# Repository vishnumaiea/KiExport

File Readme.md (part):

# KiExport

[**KiExport**](https://github.com/vishnumaiea/KiExport) is a Python application for automating the manufacturing files generation process from KiCad PCB design projects. This is a CLI (Command Line Interface) utility. Commands and arguments can be passed to the script while running, or from a JSON configuration file named `kiexport.json`. You should be familiar working with CLI tools and how to execute commands from a terminal.

KiExport generates the manufacturing files based on the options available in the `kiexport.json` file, and saves them in an organized way. It renames the files, folders and create ZIP archive files with proper names and date stamps so that you can send them to a manufacturer or client easily. Since the `kiexport.json` configuration file can be edited for any project, you only have to create the file once. You can also create multiple configuration files according to different manufacturing requirements.

The [**Mitayi Pico RP2040**](https://github.com/CIRCUITSTATE/Mitayi-Pico-RP2040) project is added as a sample project to test the script. If you are on Windows, you can run the `EXPORT-ALL.bat` batch script, or if you're on MacOS, you can run the `EXPORT-ALL.sh` script to automatically generate the manufacturing files.

This tool is not yet tested with Linux.

- **Author:** [Vishnu Mohanan](https://github.com/vishnumaiea)
- **Version:** `0.3.0`
- **Contributors:** Dominic Le Blanc ([@domleblanc94](https://github.com/domleblanc94)), Leor Weinstein

This tool was created with the help of [**ChatGPT**](https://chat.openai.com/chat). Thanks to humanity!

## Table of Contents
- [KiExport](#kiexport)
  - [Table of Contents](#table-of-contents)
  - [Why?](#why)
  - [Why not KiCad Jobsets?](#why-not-kicad-jobsets)
  - [Requirements](#requirements)
  - [Installation](#installation)
    - [Windows](#windows)
    - [MacOS](#macos)
  - [Example](#example)
  - [Usage](#usage)
  - [Commands](#commands)
    - [`version`](#version)
    - [`help`](#help)
    - [`pcb_drc`](#pcb_drc)
    - [`gerbers`](#gerbers)
    - [`drills`](#drills)
    - [`positions`](#positions)
    - [`pcb_pdf`](#pcb_pdf)
    - [`pcb_render`](#pcb_render)
    - [`sch_pdf`](#sch_pdf)
    - [`ddd`](#ddd)
    - [`pcb_svg`](#pcb_svg)
    - [`bom`](#bom)
    - [`run`](#run)
  - [Configuration File](#configuration-file)
  - [Log File](#log-file)
  - [License](#license)
  - [References](#references)

## Why?

- ~~Currently, exporting manufacturing files from KiCad's own UI requires setting so many options correctly and moving through different steps for different types of files.~~
- If you make a mistake in choosing the options correctly, you will end up with a "bad" manufacturing file that will waste your time later.
- ~~KiCad currently has no ability to save the export options as presets and it does not always remember the previously used options.~~
- Existing plugins available for KiCad only work for specific types of files and specific set of manufacturing options.
- The number and types of files generated from a KiCad project can be quite many. Renaming, organizing and archiving the files manually can be a tedious task. For example, we generate Gerbers, PCB PDF, Schematic PDF, STEP, VRML, CSV BoM, HTML BoM, XLS BoM, Position Files, and Preview Images for a typical project. We have to do this every time we make a change to the project to keep consistency across the set of files generated at a time.
- KiCad CLI can do almost all of what the KiCad UI can.
- Instead of typing the arguments manually to a terminal all the time, we can save the options as a JSON file and call the KiCad CLI every time we want to generate the files.

## Why not KiCad Jobsets?

KiCad V9 added support for **Jobsets** which allow you to generate manufacturing files in an automated way. However, the feature is in its early stages and causes freezes and crashes often (at least when I tried it last time). Until the feature matures enough, the development on KiExport will continue.

## Requirements

This software was developed and tested on Windows 11. It should work on other platforms as well, but it is not tested. The following software should be installed in your system to use this tool.

- [Python 3.x](https://www.python.org/downloads/)
- [KiCad 8.x or later](https://www.kicad.org/download/)
- [Git](https://git-scm.com/downloads) (Optional)
- [Interactive HTML BoM Plugin](https://github.com/openscopeproject/InteractiveHtmlBom) (Optional, if you want to generate HTML BoM)
- [VTracer](https://github.com/visioncortex/vtracer) (Optional, if you want to generate SVG renderings)
- Recommended:
  - [VS Code](https://code.visualstudio.com/download)
  - [Windows Terminal](https://github.com/microsoft/terminal/releases) (for Windows only)

## Installation

KiExport relies on the [**KiCad-CLI**](https://docs.kicad.org/10.0/en/cli/cli.html) tool to generate the files and therefore supports all the features of KiCad-CLI. You should have a KiCad version installed in your system to use this tool. You can download and install the latest version of KiCad from [here](https://kicad.org/download/).

### Windows

After installing KiCad, browse to the installation folder and find the `bin` directory where the `kicad-cli.exe` file is located. Add the `bin` folder to your system `PATH`. If you do not know how to add a new path to the system `PATH` variable, check out any tutorials on the internet. If you do not want to add the `kicad-cli` file to the `PATH`, then you can provide the complete path of the **kicad-cli.exe** file in the JSON configuration file using the `kicad_cli_path` parameter. This allows you to have multiple versions of KiCad and use them for different projects.

### MacOS

After installing KiCad, browse to the `Applications` folder and find the `KiCad` application icon. Right click on the icon and click "Show Package Contents" to navigate to the `Contents/MacOS` directory where the `kicad-cli` file is located. Copy the path of the `kicad-cli` file by right clicking on the file and selecting "Copy as Pathname" (for example `/Applications/KiCad/KiCad.app/Contents/MacOS/kicad-cli`) and add it to the JSON configuration file using the `kicad_cli_path` parameter. This allows you to have multiple versions of KiCad and use them for different projects.

You can clone/fork the project to obtain a copy of the repository in your system using the following command. [Git](https://git-scm.com/downloads) should be installed and available on the path.

```bash
git clone https://github.com/vishnumaiea/KiExport.git
```

Additionally, you can download the project as a ZIP file from the main page or the [Releases](/releases) page and extract it in your system. After getting the files, you can add the project folder to the system `PATH` variable. If your system opens Python script files with the Python interpreter by default, you can run any python script directly from the terminal even without using the `.py` extension as shown in the image below.

If it still says "kiexport" is not a valid command, add the `.PY` extension to the `PATHEXT` system environment variable in Windows as shown below.

If you are going to run the app as a Python script, install the dependencies using the following command.

```bash
pip install -r requirements.txt
```

Additionally, the app can tell you which dependencies are missing in most cases, and guide you to install them. If you do not want to run KiEXport as a Python script, or if you do not want to setup Python in your system, then you can use the Windows executable directly. The executable is available in the [`dist`](/dist/) folder. You can add the `dist` folder to your system `PATH` variable to run the app from anywhere in the terminal.

Check if the app is working by checking the version of the tool. Open a terminal and run the following command.

```bash
kiexport -v
```

If you see the version printed, the installation is successful. Otherwise, follow the installation procedure again.

## Example

Following is a tree view of the files generated by KiExport from the **Mitayi-Pico-D1** project. A top level revision folder will be created to store the files for that specific revision. Under that, a date-specific folder will be created to store files generated in a specific day. Inside that, file-specific folders are created to store the different types of files. ZIP archives are created for some type of files that are usually sent as a set of files to the manufacturer, for example Gerbers.

If you generate the files multiple times a day, older files will be overwritten except for any files with a sequence number at the end of the filename. For example, ZIP files have a sequence number at the end of the filename after the date string. A new file with a new sequence number will be created when multiple files are generated.

```
\---R0.6
    \---2024-10-26
        +---3D
        |       Mitayi-Pico-RP2040-R0.6-STEP-26102024-1.step
        |       Mitayi-Pico-RP2040-R0.6-VRML-26102024-1.wrl
        |       Mitayi-Pico-RP2040-R0.6-3DPDF-26102024-1.pdf
        |
        +---Position
        |       Mitayi-Pico-RP2040-R0.6-Position-All.csv
        |       Mitayi-Pico-RP2040-R0.6-Position-Back.csv 
        |       Mitayi-Pico-RP2040-R0.6-Position-Front.csv
        |       Mitayi-Pico-RP2040-R0.6-Position-Files-26102024-1.zip
        |
        +---BoM
        |       Mitayi-Pico-RP2040-R0.6-BoM-CSV-26102024-1.csv
        |       Mitayi-Pico-RP2040-R0.6-BoM-XLS-26102024-1.xlsx
        |       Mitayi-Pico-RP2040-R0.6-BoM-HTML-26102024-1.html
        |
        +---Gerber
        |       Mitayi-Pico-RP2040-R0.6-B_Courtyard.gbr
        |       Mitayi-Pico-RP2040-R0.6-B_Cu.gbr
        |       Mitayi-Pico-RP2040-R0.6-B_Fab.gbr
        |       Mitayi-Pico-RP2040-R0.6-B_Mask.gbr
        |       Mitayi-Pico-RP2040-R0.6-B_Paste.gbr
        |       Mitayi-Pico-RP2040-R0.6-B_Silkscreen.gbr
        |       Mitayi-Pico-RP2040-R0.6-Edge_Cuts.gbr
        |       Mitayi-Pico-RP2040-R0.6-F_Courtyard.gbr
        |       Mitayi-Pico-RP2040-R0.6-F_Cu.gbr
        |       Mitayi-Pico-RP2040-R0.6-F_Fab.gbr
        |       Mitayi-Pico-RP2040-R0.6-F_Mask.gbr
        |       Mitayi-Pico-RP2040-R0.6-F_Paste.gbr
        |       Mitayi-Pico-RP2040-R0.6-F_Silkscreen.gbr
        |       Mitayi-Pico-RP2040-R0.6-Gerber-26102024-1.zip
        |       Mitayi-Pico-RP2040-R0.6-job.gbrjob
        |       Mitayi-Pico-RP2040-R0.6-NPTH-drl_map.pdf
        |       Mitayi-Pico-RP2040-R0.6-NPTH.drl
        |       Mitayi-Pico-RP2040-R0.6-PTH-drl_map.pdf
        |       Mitayi-Pico-RP2040-R0.6-PTH.drl
        |       Mitayi-Pico-RP2040-R0.6-User_Comments.gbr
        |       Mitayi-Pico-RP2040-R0.6-User_Drawings.gbr
        |
        +---PCB
        |       Mitayi-Pico-RP2040-R0.6-B_Courtyard.pdf
        |       Mitayi-Pico-RP2040-R0.6-B_Cu.pdf
        |       Mitayi-Pico-RP2040-R0.6-B_Fab.pdf
        |       Mitayi-Pico-RP2040-R0.6-B_Mask.pdf
        |       Mitayi-Pico-RP2040-R0.6-B_Paste.pdf
        |       Mitayi-Pico-RP2040-R0.6-B_Silkscreen.pdf
        |       Mitayi-Pico-RP2040-R0.6-Edge_Cuts.pdf
        |       Mitayi-Pico-RP2040-R0.6-F_Courtyard.pdf
        |       Mitayi-Pico-RP2040-R0.6-F_Cu.pdf
        |       Mitayi-Pico-RP2040-R0.6-F_Fab.pdf
        |       Mitayi-Pico-RP2040-R0.6-F_Mask.pdf
        |       Mitayi-Pico-RP2040-R0.6-F_Paste.pdf
        |       Mitayi-Pico-RP2040-R0.6-F_Silkscreen.pdf
        |       Mitayi-Pico-RP2040-R0.6-PCB-PDF-26102024-1.zip
        |       Mitayi-Pico-RP2040-R0.6-PCB-PDF-All-26102024-1.pdf
        |       Mitayi-Pico-RP2040-R0.6-User_Comments.pdf
        |       Mitayi-Pico-RP2040-R0.6-User_Drawings.pdf
        |
        +---Render
        |       Mitayi-Pico-RP2040-R0.6-Top-26102024-1.png
        |       Mitayi-Pico-RP2040-R0.6-Top-26102024-1-Cropped.png
        |       Mitayi-Pico-RP2040-R0.6-Top-26102024-1-Cropped.svg
        |       Mitayi-Pico-RP2040-R0.6-Bottom-26102024-1.png
        |       Mitayi-Pico-RP2040-R0.6-Bottom-26102024-1-Cropped.png
        |       Mitayi-Pico-RP2040-R0.6-Bottom-26102024-1-Cropped.svg
        |       Mitayi-Pico-RP2040-R0.6-Front-26102024-1.png
        |       Mitayi-Pico-RP2040-R0.6-Front-26102024-1-Cropped.png
        |       Mitayi-Pico-RP2040-R0.6-Front-26102024-1-Cropped.svg
        |       Mitayi-Pico-RP2040-R0.6-Back-26102024-1.png
        |       Mitayi-Pico-RP2040-R0.6-Back-26102024-1-Cropped.png
        |       Mitayi-Pico-RP2040-R0.6-Back-26102024-1-Cropped.svg
        |
        +---Report
        |       Mitayi-Pico-RP2040-R0.6-DRC-26102024-1.rpt
        |       Mitayi-Pico-RP2040-R0.6-DRC-26102024-1.json
        |
        +---SCH
        |       Mitayi-Pico-RP2040-R0.6-SCH-26102024-1.pdf
        |
        \---SVG
                Mitayi-Pico-RP2040-R0.6-B_Courtyard.svg
                Mitayi-Pico-RP2040-R0.6-B_Cu.svg
                Mitayi-Pico-RP2040-R0.6-B_Fab.svg
                Mitayi-Pico-RP2040-R0.6-B_Mask.svg
                Mitayi-Pico-RP2040-R0.6-B_Paste.svg
                Mitayi-Pico-RP2040-R0.6-B_Silkscreen.svg
                Mitayi-Pico-RP2040-R0.6-Edge_Cuts.svg
                Mitayi-Pico-RP2040-R0.6-F_Courtyard.svg
                Mitayi-Pico-RP2040-R0.6-F_Cu.svg
                Mitayi-Pico-RP2040-R0.6-F_Fab.svg
                Mitayi-Pico-RP2040-R0.6-F_Mask.svg
                Mitayi-Pico-RP2040-R0.6-F_Paste.svg
                Mitayi-Pico-RP2040-R0.6-F_Silkscreen.svg
                Mitayi-Pico-RP2040-R0.6-PCB-SVG-25102025-1.zip
                Mitayi-Pico-RP2040-R0.6-User_Comments.svg
                Mitayi-Pico-RP2040-R0.6-User_Drawings.svg
```

## Usage

After installing KiExport, you can create a new `kiexport.json` file inside the root folder of your KiCad project. You can also copy the configuration file included with the [**Mitayi-Pico-RP2040**](/Mitayi-Pico-D1/kiexport.json) project and modify it. You need to update the KiCad installation path, secondary application paths, and project information. After that, you can run the Python script directly from the source folder with the following command. Python should be installed and available on the `Path`.

```bash
python kiexport.py <command> <arguments>
```

In addition, you can also run the Windows executable `kiexport.exe` with the following command. The `dist` folder should be added to the system `Path` in order for this to work.

```bash
kiexport <command> <arguments>
```

You can automate running multiple commands with a batch script if you are on Windows. Refer to the [`EXPORT-ALL.bat`](/Mitayi-Pico-D1/EXPORT-ALL.bat) file for an example. Run the script to see KiExport in action.

```bat
@REM @echo off

:: Set variables
set OUTPUT_DIR=Export
set SCH_FILE=Mitayi-Pico-D1.kicad_sch
set PCB_FILE=Mitayi-Pico-D1.kicad_pcb

:: Execute commands
@REM kiexport pcb_drc -od "%OUTPUT_DIR%" -if "%PCB_FILE%" -t "report"
@REM kiexport sch_pdf -od "%OUTPUT_DIR%" -if "%SCH_FILE%"
@REM kiexport bom -od "%OUTPUT_DIR%" -if "%SCH_FILE%" -t "CSV"
@REM kiexport bom -od "%OUTPUT_DIR%" -if "%SCH_FILE%" -t "XLS"
@REM kiexport bom -od "%OUTPUT_DIR%" -if "%PCB_FILE%" -t "HTML"
@REM kiexport pcb_pdf -od "%OUTPUT_DIR%" -if "%PCB_FILE%"
@REM kiexport pcb_render -od "%OUTPUT_DIR%" -if "%PCB_FILE%"
@REM kiexport gerbers -od "%OUTPUT_DIR%" -if "%PCB_FILE%"
@REM kiexport positions -od "%OUTPUT_DIR%" -if "%PCB_FILE%"
@REM kiexport ddd -od "%OUTPUT_DIR%" -if "%PCB_FILE%" -t "STEP"
@REM kiexport ddd -od "%OUTPUT_DIR%" -if "%PCB_FILE%" -t "VRML"
@REM kiexport ddd -od "%OUTPUT_DIR%" -if "%PCB_FILE%" -t "3DPDF"

pause
```

You can also create a batch file for running the `run` command as shown below. You can then double-click on the script every time you want to generate new files, saving you from typing the same commands over and over.

```bash
kiexport run Mitayi-Pico-D1/kiexport.json

pause
```

If you're on MacOS, you can create a shell script to run the commands. Refer to the [`EXPORT-ALL.sh`](/Mitayi-Pico-D1/EXPORT-ALL.sh) file for an example.

```bash
#!/bin/bash

# 1. Force the shell to read aliases inside scripts
shopt -s expand_aliases 2>/dev/null || set -o aliases

# 2. Source your profile to load the 'kiexport' alias
source ~/.zshrc

kiexport run "kiexport-mac.json"

# Pause script (macOS equivalent of windows "pause")
read -p "Press [Enter] key to continue..."
```

## Commands

### `version`

Run the following command to show the version of the tool.

```bash
kiexport -v
```

```bash
kiexport --version
```

### `help`

Show the help menu.

```bash
kiexport -h
```

```bash
kiexport --help
```

You can include the command to get the help menu of a specific command. For example,

```bash
kiexport gerbers -h
```

### `pcb_drc`

Runs a DRC (Design Rule Check) on the PCB file. If there are errors in the design, evaluated as per the DRC rules, the command will return the type and number of errors found. It will also generate a report file and save it to the output directory. When ran as part of the `run` command, you can choose to skip other commands if there are DRC errors. The configuration for this command can be specified in the configuration file under the `pcb_drc` section. If a format type is specified in the CLI command, it will override the type specified in the configuration file.

```bash
kiexport pcb_drc -if <input_file> -od <output_dir> -t <type>
```

- `-if`: Path to the input `.kicad_pcb` file. Required.
- `-od`: Path to the output directory where the report will be saved. Required.
- `-t`: The type of report to generate. Possible values are `report`, and `json`. Optional. Defaults to the type specified in the configuration file.
  - `report` - Generates a text report file with `.rpt` extension.
  - `json` - Generates a JSON report file with `.json` extension.

### `gerbers`

Export the Gerber files. Gerber files export does not include the drill files by default. If you want to generate the drill files as well, you can either manually run the `drills` command or enable the drill file generation in the JSON configuration file using the `kie_include_drill` flag.

```bash
kiexport gerbers -if <input_file> -od <output_dir>
```

- `-if`: Path to the input `.kicad_pcb` file. Required.
- `-od`: Path to the output directory. Required.

Example:

```bash
kiexport gerbers -if "Mitayi-Pico-D1/Mitayi-Pico-RP2040.kicad_pcb" -od "Mitayi-Pico-D1/Export"
```

### `drills`

Generate the drill files. If you are generating drill files along with the `gerbers` command, you don't need to run this command again. Otherwise, the drill files will be generated twice.

```bash
kiexport drills -if <input_file> -od <output_dir>
```

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
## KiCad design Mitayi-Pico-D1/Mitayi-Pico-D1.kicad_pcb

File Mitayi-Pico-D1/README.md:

View this project on [CADLAB.io](https://cadlab.io/project/25932). 

# Mitayi Pico R0.6

**Mitayi Pico** is the first development board from **CIRCUITSTATE Electronics**. It is a small development board based on the **RP2040** microcontroller from Raspberry Pi. The board is designed after the official Pico board from Raspberry Pi, but adds a few improvements over it.

The schematic and PCB are designed with **KiCad**, an open-source EDA tool. All the design files of Mitayi Pico are completely open-source and released under the MIT license.

## Features & Differences

* RP2040 dual-core, 133MHz ARM Cortex M0+ microcontroller.
* Up to 16MB Flash memory in SOIC-8 package.
* Dual USB port options; Type-C and Micro-USB.
* Linear Low-drop voltage regulator MIC5219.
* Reset button.
* BOOTSEL button.
* Solder jumper on debug LED.
* Breaks out all GPIO pins.
* EXP8 expansion connector in 2x4 2.54mm pin header. Breaks out SPI, UART and I2C.
* Uses 0402 or larger SMD packages.
* **Mitayi-Pico is not pin-compatible with the official Raspberry Pi Pico.**
* Same dimensions of 21 mm x 50 mm, with almost the same positions for mounting holes.
* Completely open-source design made with KiCad 7.

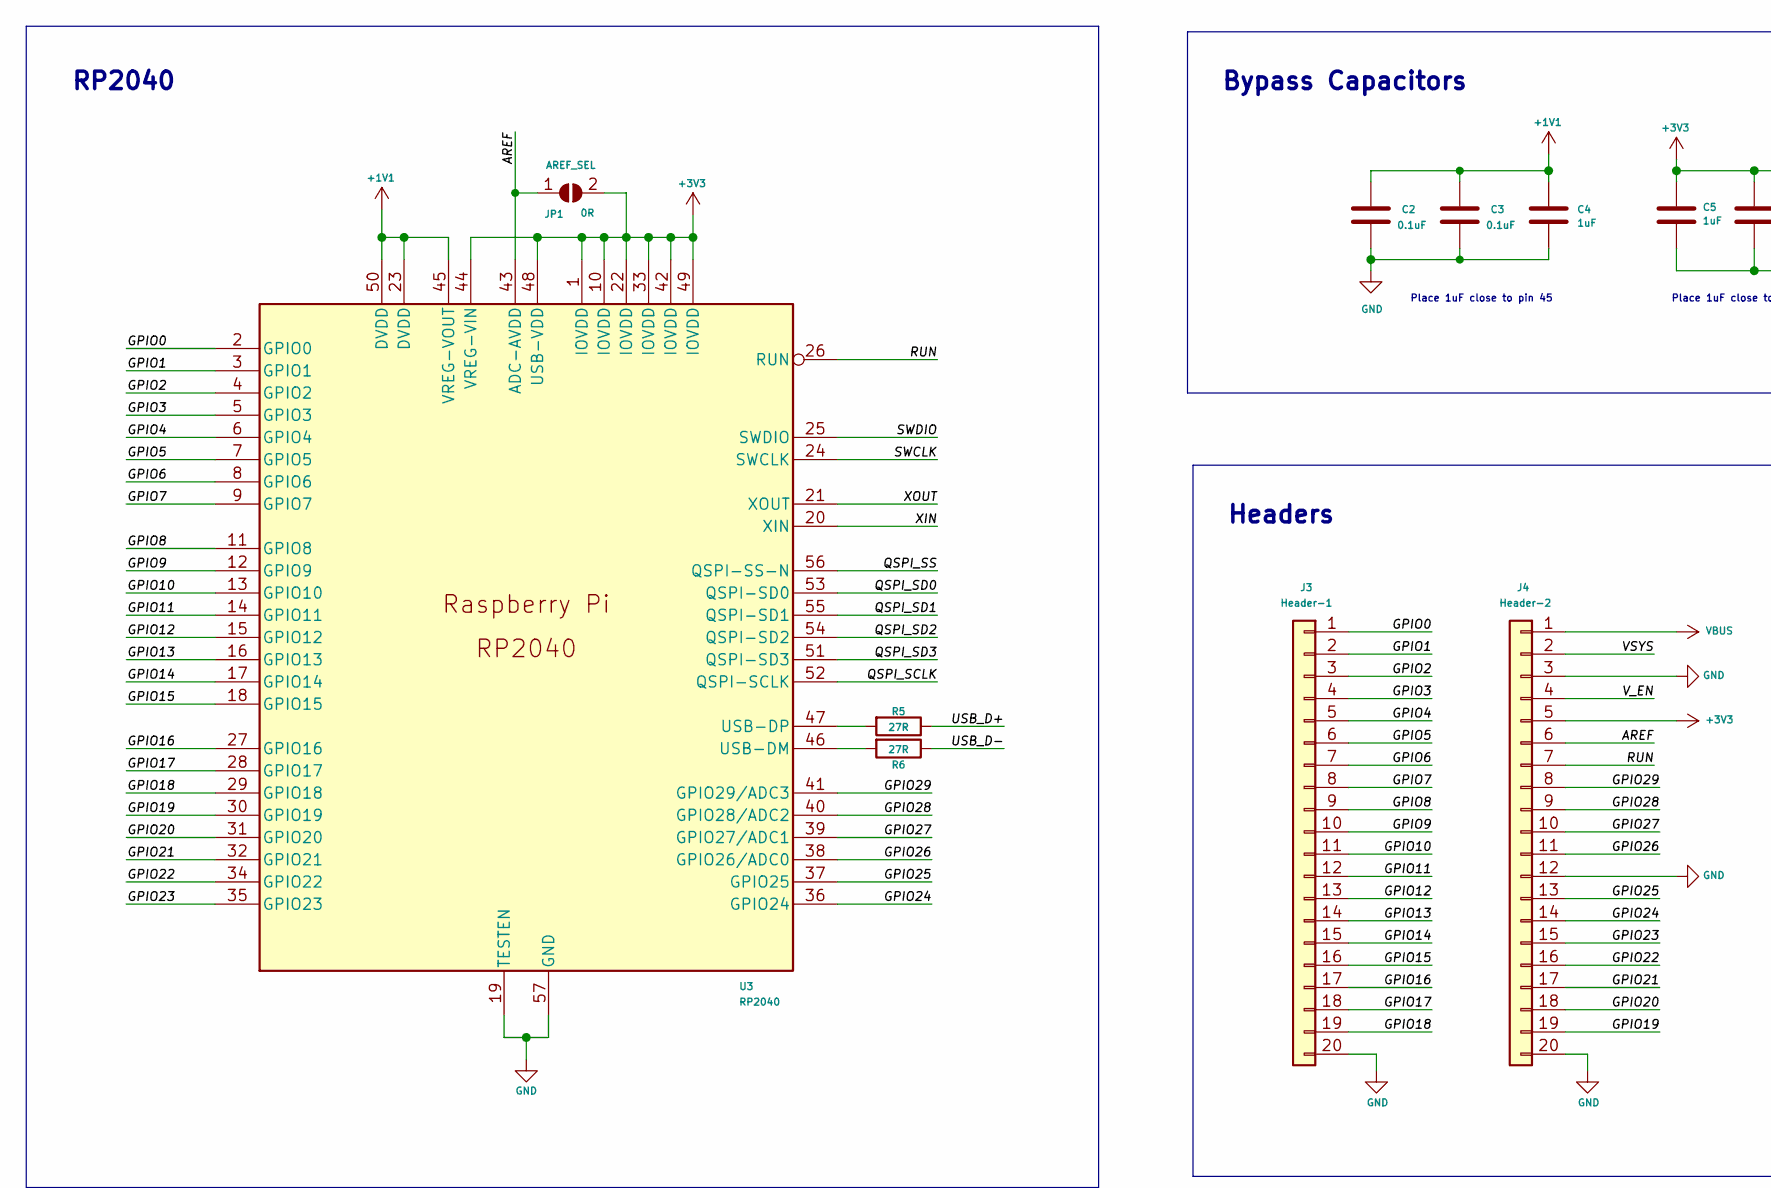
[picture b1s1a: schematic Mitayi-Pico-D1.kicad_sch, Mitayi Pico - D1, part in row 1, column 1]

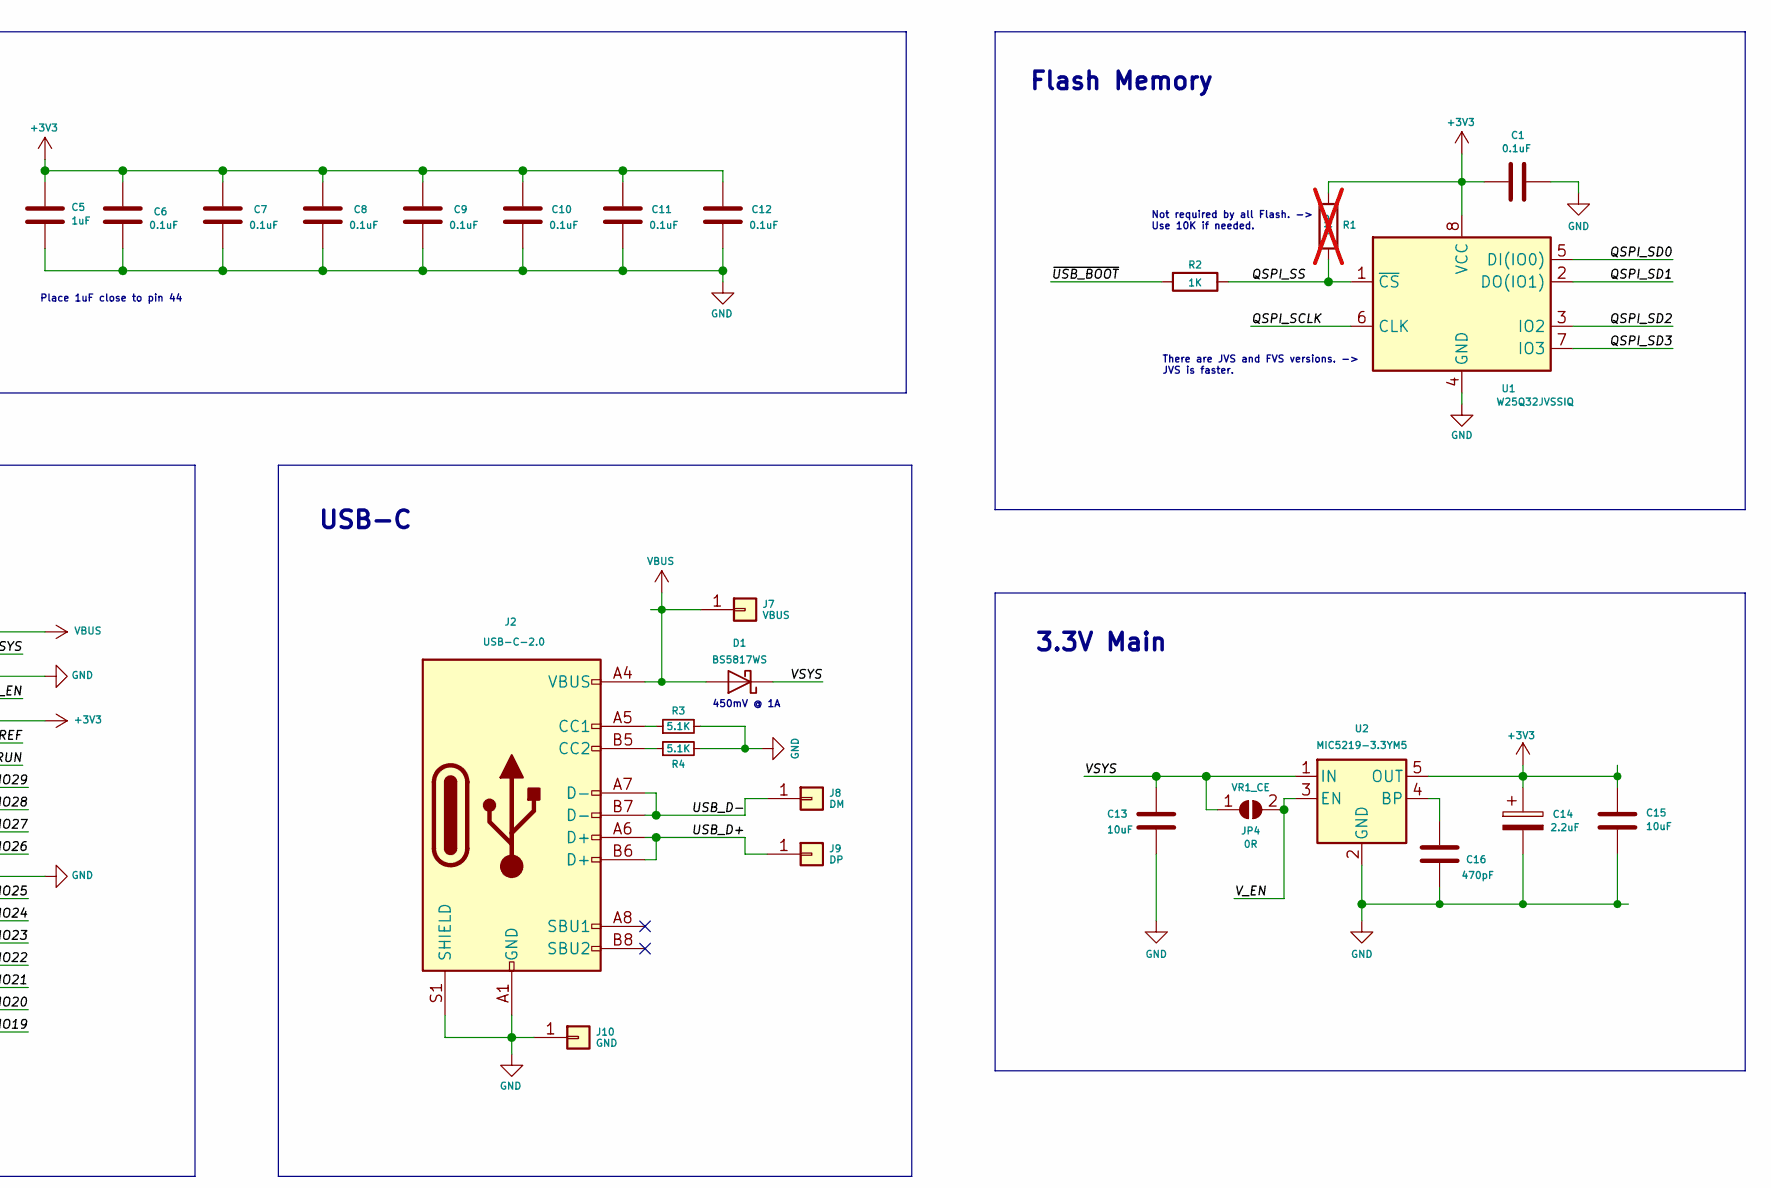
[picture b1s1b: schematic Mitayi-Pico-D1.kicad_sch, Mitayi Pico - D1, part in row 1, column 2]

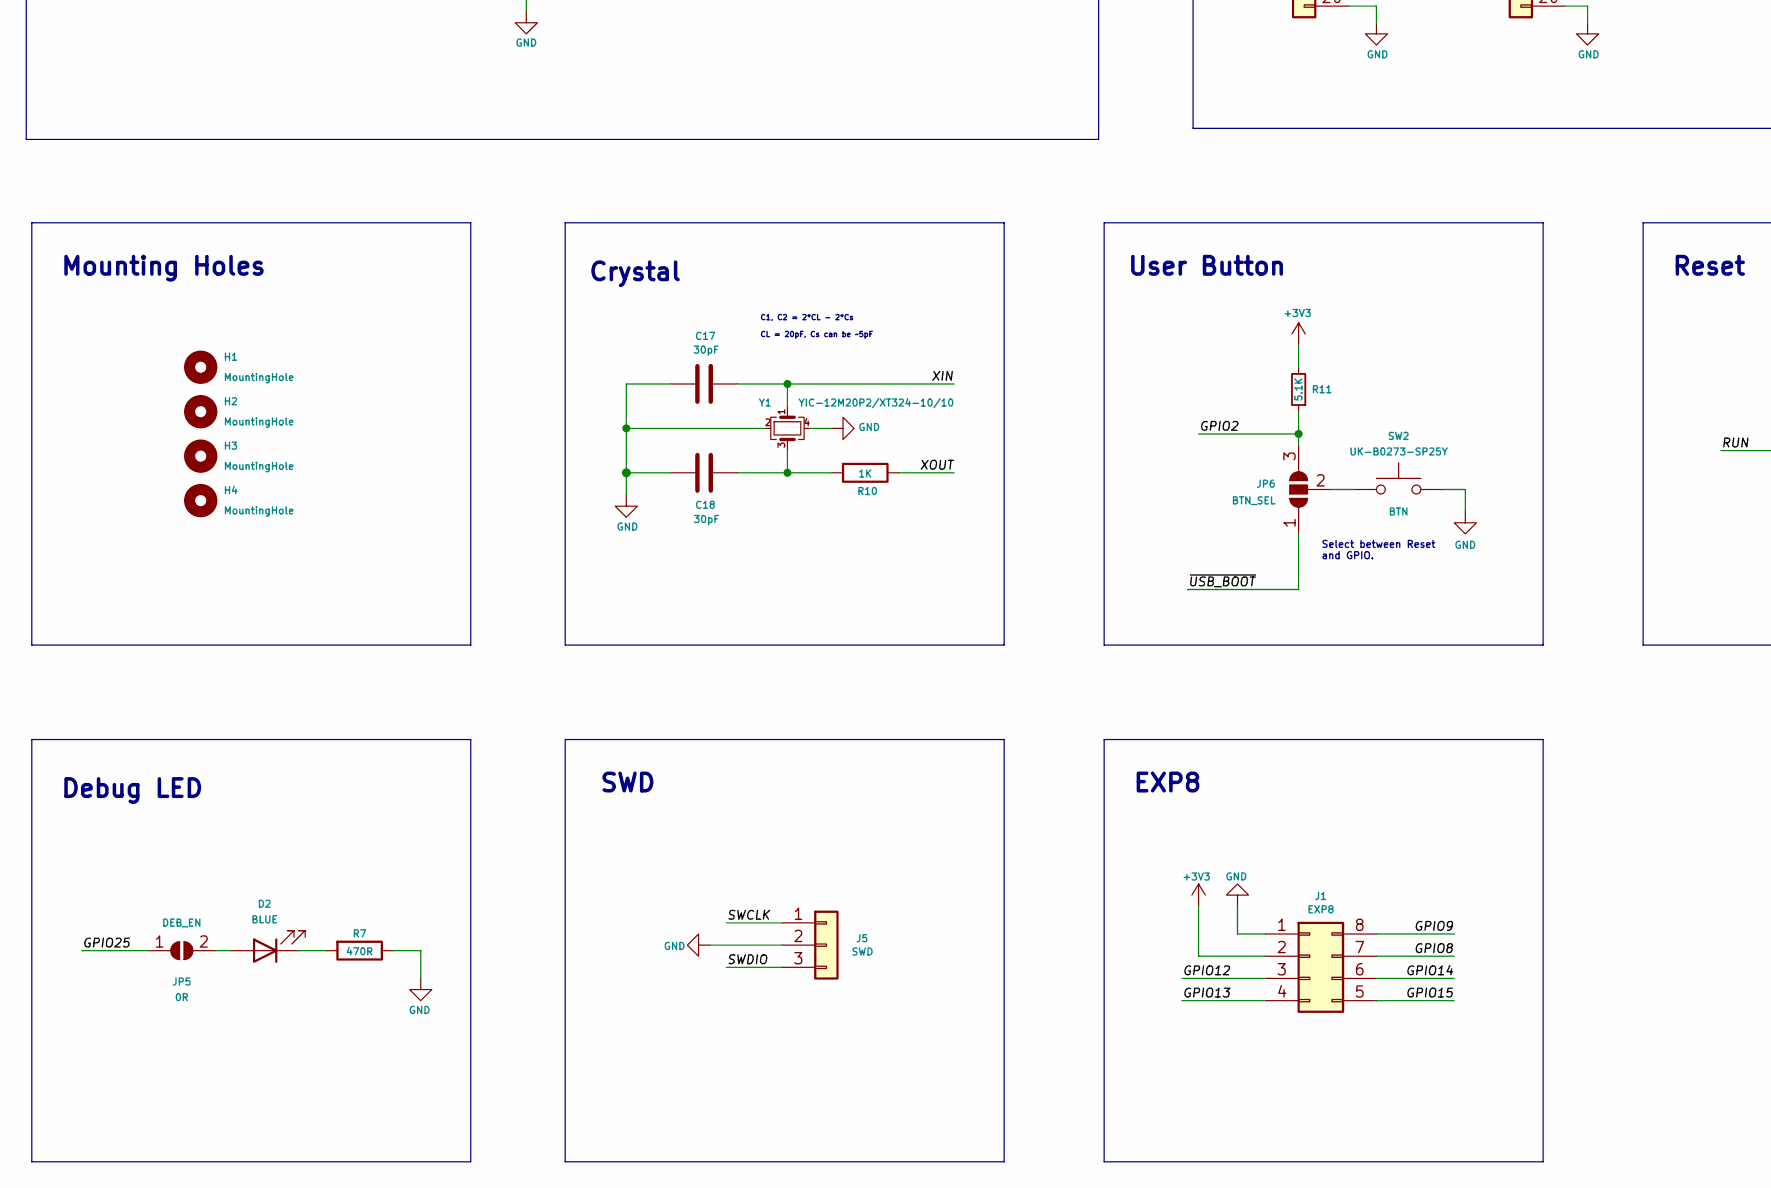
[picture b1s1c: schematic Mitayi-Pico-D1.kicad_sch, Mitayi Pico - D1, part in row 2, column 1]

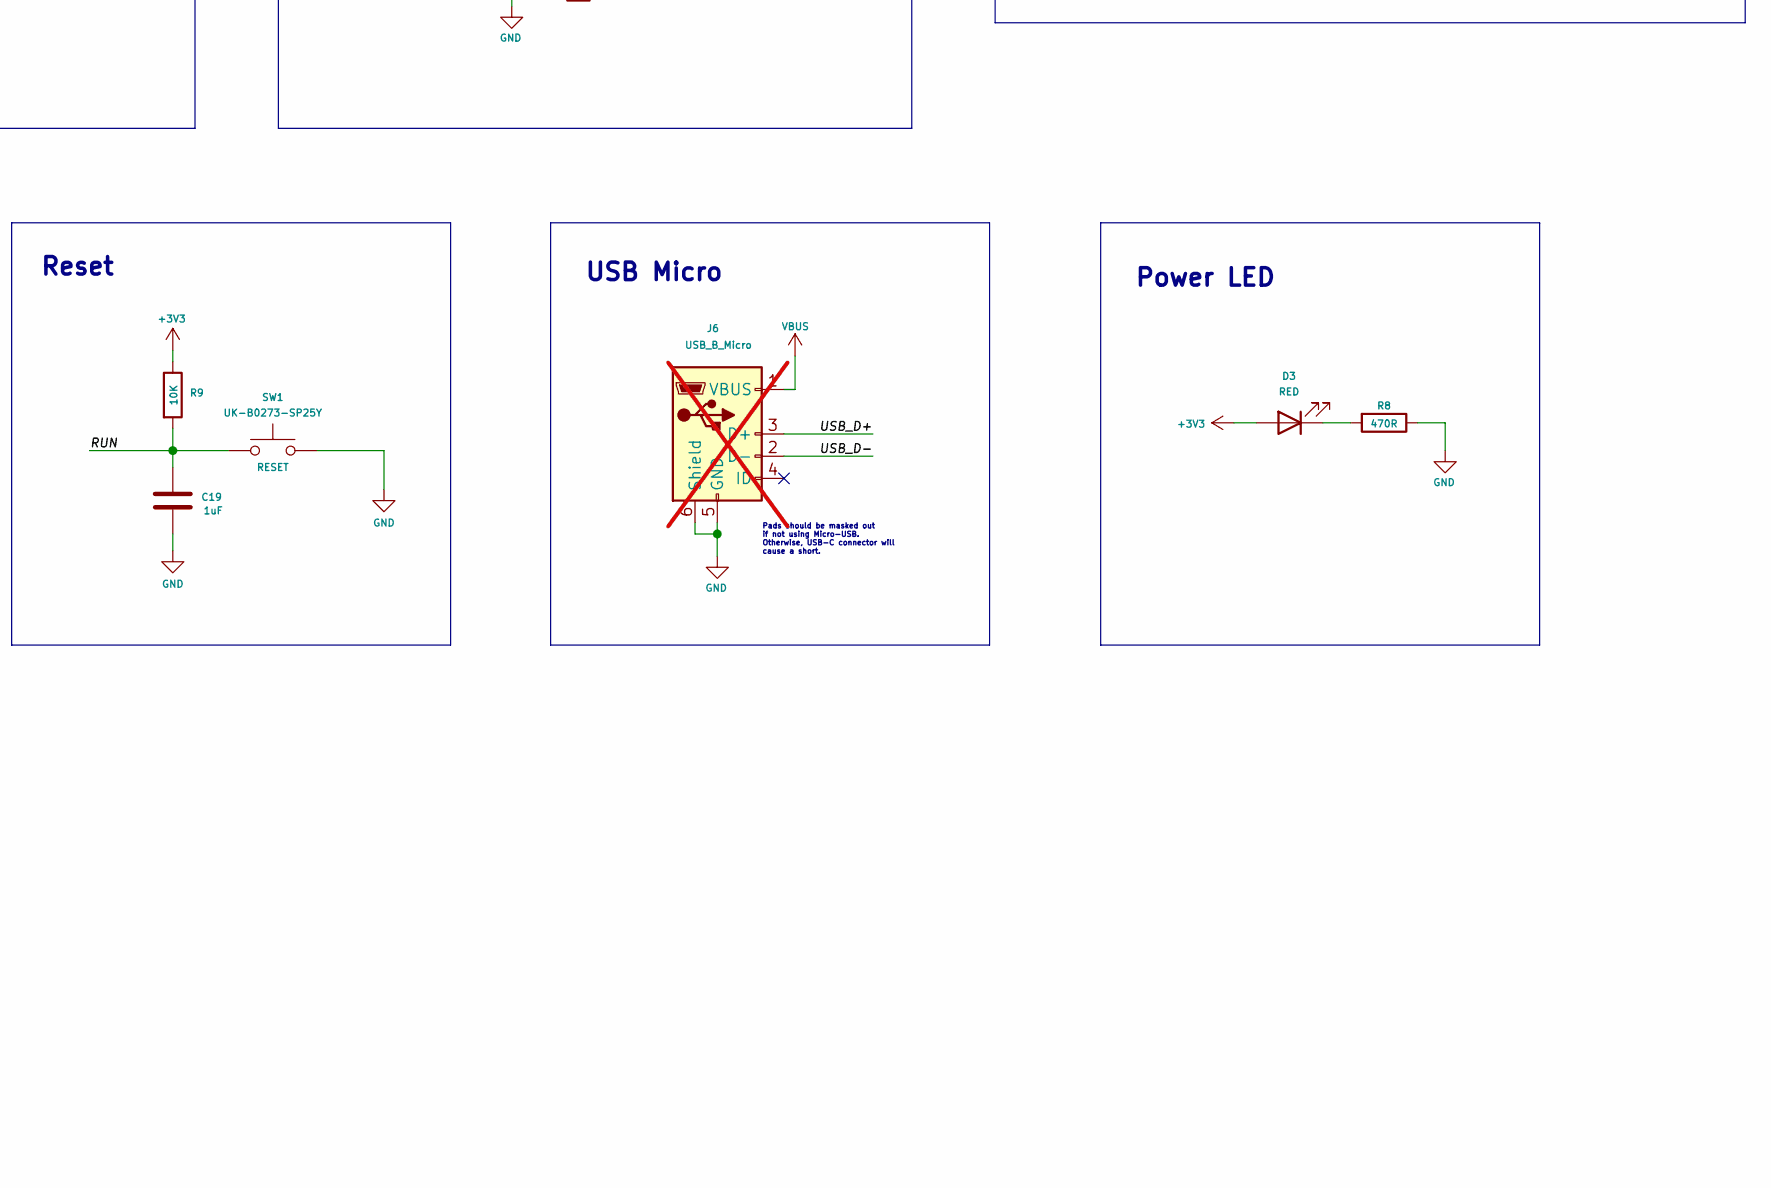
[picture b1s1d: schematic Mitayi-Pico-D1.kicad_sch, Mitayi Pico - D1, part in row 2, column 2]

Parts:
C1, C2, C3, C6, C7, C8, C9, C10, C11, C12: 0.1uF; C_0402_1005Metric; MPN 0402B104K160CT
C4, C5, C19: 1uF; C_0402_1005Metric; MPN 0402X105K160CT
C13, C15: 10uF; C_0603_1608Metric; MPN 0603X106M6R3CT
C14: 2.2uF; CP_EIA-2012-12_Kemet-R; MPN TAJR225M016RNJ
C16: 470pF; C_0402_1005Metric; MPN 0402N471J500LT
C17, C18: 30pF; C_0402_1005Metric; MPN 0402N270J500LT
D1: BS5817WS; D_SOD-323_HandSoldering; MPN B5817WS
D2: BLUE; LED_0603_1608Metric; MPN 19-213/BHC-ZL1M2RY/3T
D3: RED; LED_0603_1608Metric; MPN 19-21SURC/S530-A2/TR8
H1, H2, H3, H4: MountingHole; MountingHole_2.2mm_M2; MPN DNP
J1: EXP8; PinHeader_2x04_P2.54mm_Vertical; MPN DNP
J2: USB-C-2.0; USB_C_Receptacle_HRO_TYPE-C-31-M-12; MPN HC-TYPE-C-16P-01A
J3: Header-1; PinHeader_1x20_2H_P2.54mm_Vertical; MPN DNP
J4: Header-2; PinHeader_1x20_2H_P2.54mm_Vertical; MPN DNP
J5: SWD; PinHeader_1x03_P2.54mm_Vertical; MPN DNP
J6: USB_B_Micro; USB_Micro-B_Molex-105017-0001; MPN DNP; not fitted
J7: VBUS; Solderpad_Rounded_Rectangle_0.8x1.3mm; MPN DNP
J8: DM; Solderpad_Rounded_Rectangle_0.8x1.3mm; MPN DNP
J9: DP; Solderpad_Rounded_Rectangle_0.8x1.3mm; MPN DNP
J10: GND; Solderpad_Rectangle_0.8x1.3mm_Chamfered; MPN DNP
JP1, JP4, JP5: 0R; R_0402_1005Metric_Pad0.72x0.64mm_HandSolder; MPN WR04X000PTL
JP6: BTN_SEL; SolderJumper-3_P0.83mm_Open_Rounded-Pad_0.85x1mm; MPN DNP
R1: DNP; R_0402_1005Metric; MPN DNP; not fitted
R2, R10: 1K; R_0402_1005Metric; MPN WR04X1001FTL
R3, R4, R11: 5.1K; R_0402_1005Metric; MPN WR04X5101FTL
R5, R6: 27R; R_0402_1005Metric; MPN WR04X27R0FTL
R7, R8: 470R; R_0402_1005Metric; MPN WR04X4700FTL
R9: 10K; R_0402_1005Metric; MPN WR04X1002FTL
SW1, SW2: UK-B0273-SP25Y; CK_SW_SPST_UK-B0273-SP25Y; MPN UK-B0273-SP25Y
U1: W25Q32JVSSIQ; SOIC-8_5.23x5.23mm_P1.27mm; MPN W25Q32JVSSIQ
U2: MIC5219-3.3YM5; SOT-23-5; MPN MIC5219-3.3YM5-TR
U3: RP2040; RP2040-QFN-56; MPN RP2040-B2
Y1: YIC-12M20P2/XT324-10/10; Crystal_SMD_3225-4Pin_3.2x2.5mm; MPN YIC-12M20P2/XT324-10/10

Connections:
+1V1: C2.1, C3.1, C4.1, U3.23 (DVDD), U3.45 (VREG-VOUT), U3.50 (DVDD)
+3V3: C1.1, C5.1, C6.1, C7.1, C8.1, C9.1, C10.1, C11.1, C12.1, C14.1, C15.1, D3.2 (A), J1.2, J4.5, JP1.2 (B), R1.1, R9.1, R11.2, U1.8 (VCC), U2.5 (OUT), U3.1 (IOVDD), U3.10 (IOVDD), U3.22 (IOVDD), U3.33 (IOVDD), U3.42 (IOVDD), U3.44 (VREG-VIN), U3.48 (USB-VDD), U3.49 (IOVDD)
/AREF: J4.6, JP1.1 (A), U3.43 (ADC-AVDD)
/GPIO0: J3.1, U3.2 (GPIO0)
/GPIO1: J3.2, U3.3 (GPIO1)
/GPIO2: J3.3, JP6.3 (B), R11.1, U3.4 (GPIO2)
/GPIO3: J3.4, U3.5 (GPIO3)
/GPIO4: J3.5, U3.6 (GPIO4)
/GPIO5: J3.6, U3.7 (GPIO5)
/GPIO6: J3.7, U3.8 (GPIO6)
/GPIO7: J3.8, U3.9 (GPIO7)
/GPIO8: J1.7, J3.9, U3.11 (GPIO8)
/GPIO9: J1.8, J3.10, U3.12 (GPIO9)
/GPIO10: J3.11, U3.13 (GPIO10)
/GPIO11: J3.12, U3.14 (GPIO11)
/GPIO12: J1.3, J3.13, U3.15 (GPIO12)
/GPIO13: J1.4, J3.14, U3.16 (GPIO13)
/GPIO14: J1.6, J3.15, U3.17 (GPIO14)
/GPIO15: J1.5, J3.16, U3.18 (GPIO15)
/GPIO16: J3.17, U3.27 (GPIO16)
/GPIO17: J3.18, U3.28 (GPIO17)
/GPIO18: J3.19, U3.29 (GPIO18)
/GPIO19: J4.19, U3.30 (GPIO19)
/GPIO20: J4.18, U3.31 (GPIO20)
/GPIO21: J4.17, U3.32 (GPIO21)
/GPIO22: J4.16, U3.34 (GPIO22)
/GPIO23: J4.15, U3.35 (GPIO23)
/GPIO24: J4.14, U3.36 (GPIO24)
/GPIO25: J4.13, JP5.1 (A), U3.37 (GPIO25)
/GPIO26: J4.11, U3.38 (GPIO26/ADC0)
/GPIO27: J4.10, U3.39 (GPIO27/ADC1)
/GPIO28: J4.9, U3.40 (GPIO28/ADC2)
/GPIO29: J4.8, U3.41 (GPIO29/ADC3)
/QSPI_SCLK: U1.6 (CLK), U3.52 (QSPI-SCLK)
/QSPI_SD0: U1.5 (DI(IO0)), U3.53 (QSPI-SD0)
/QSPI_SD1: U1.2 (DO(IO1)), U3.55 (QSPI-SD1)
/QSPI_SD2: U1.3 (IO2), U3.54 (QSPI-SD2)
/QSPI_SD3: U1.7 (IO3), U3.51 (QSPI-SD3)
/QSPI_SS: R1.2, R2.1, U1.1 (~CS), U3.56 (QSPI-SS-N)
/RUN: C19.1, J4.7, R9.2, SW1.1, U3.26 (RUN)
/SWCLK: J5.1, U3.24 (SWCLK)
/SWDIO: J5.3, U3.25 (SWDIO)
/USB_D+: J2.A6 (D+), J2.B6 (D+), J6.3 (D+), J9.1, R5.1
/USB_D-: J2.A7 (D-), J2.B7 (D-), J6.2 (D-), J8.1, R6.1
/VSYS: C13.1, D1.1 (K), J4.2, JP4.1 (A), U2.1 (IN)
/V_EN: J4.4, JP4.2 (B), U2.3 (EN)
/XIN: C17.1, U3.20 (XIN), Y1.1
/XOUT: R10.1, U3.21 (XOUT)
/~USB_BOOT: JP6.1 (A), R2.2
GND: C1.2, C2.2, C3.2, C4.2, C5.2, C6.2, C7.2, C8.2, C9.2, C10.2, C11.2, C12.2, C13.2, C14.2, C15.2, C16.2, C17.2, C18.2, C19.2, J1.1, J2.A1 (GND), J2.A12 (GND), J2.B1 (GND), J2.B12 (GND), J2.S1 (SHIELD), J3.20, J4.3, J4.12, J4.20, J5.2, J6.5 (GND), J6.6 (Shield), J10.1, R3.2, R4.2, R7.1, R8.1, SW1.2, SW2.2, U1.4 (GND), U2.2 (GND), U3.19 (TESTEN), U3.57 (GND), Y1.2, Y1.4
unnamed: C18.1, R10.2, Y1.3
unnamed: D2.2 (A), JP5.2 (B)
unnamed: D2.1 (K), R7.2
unnamed: D3.1 (K), R8.2
unnamed: J2.A5 (CC1), R3.1
unnamed: J2.B5 (CC2), R4.1
unnamed: JP6.2 (C), SW2.1
unnamed: C16.1, U2.4 (BP)
unnamed: R6.2, U3.46 (USB-DM)
unnamed: R5.2, U3.47 (USB-DP)
VBUS: D1.2 (A), J2.A4 (VBUS), J2.A9 (VBUS), J2.B4 (VBUS), J2.B9 (VBUS), J4.1, J6.1 (VBUS), J7.1

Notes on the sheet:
Headers
3.3V Main
450mV @ 1A
Power LED
Place 1uF close to pin 45
There are JVS and FVS versions. -> JVS is faster.
RP2040
EXP8
Pads should be masked out if not using Micro-USB. Otherwise, USB-C connector will cause a short.
Flash Memory
Not required by all Flash. -> Use 10K if needed.
C1, C2 = 2*CL - 2*Cs CL = 20pF, Cs can be ~5pF
SWD
Reset
USB Micro
Place 1uF close to pin 44
Crystal
Select between Reset and GPIO.
Mounting Holes
Bypass Capacitors
USB-C
Debug LED
User Button

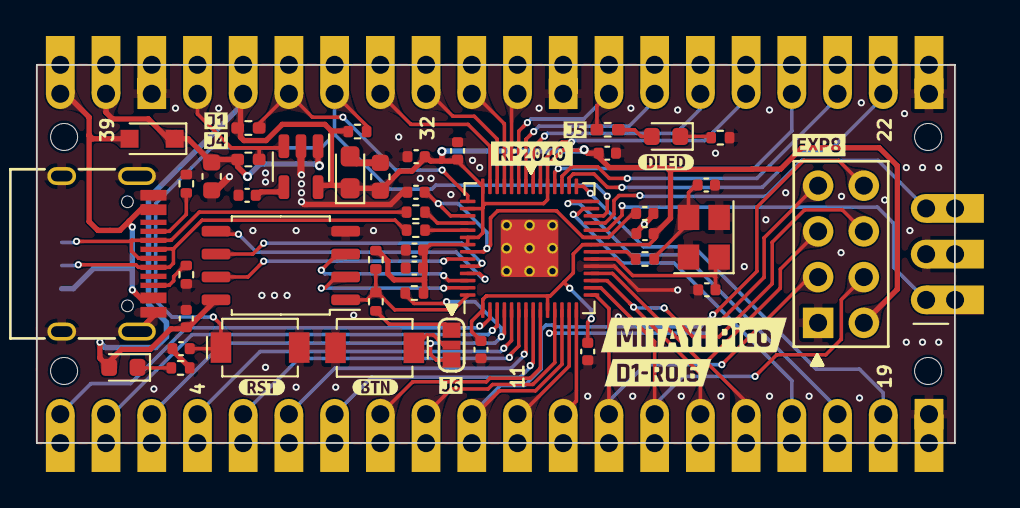
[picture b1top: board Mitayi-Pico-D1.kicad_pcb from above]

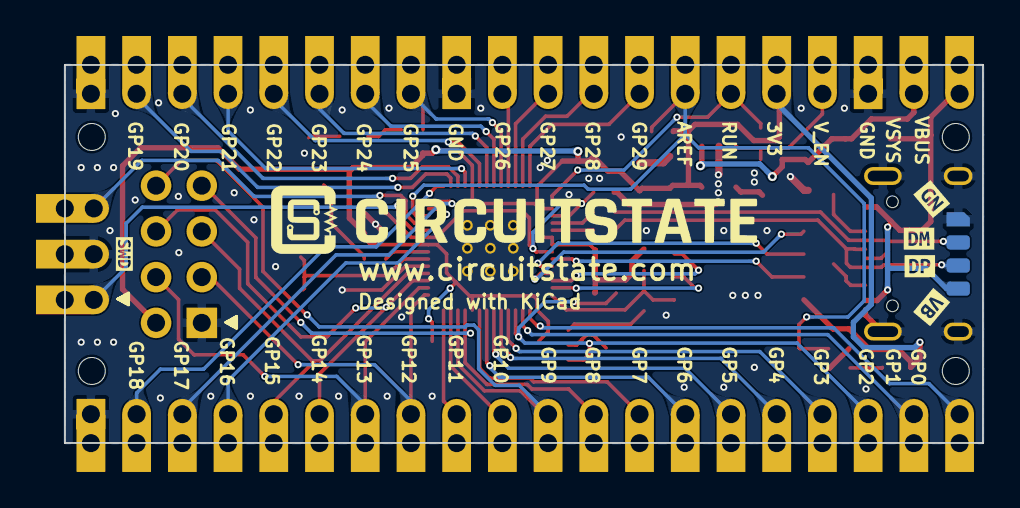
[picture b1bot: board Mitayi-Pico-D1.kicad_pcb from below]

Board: 2 copper layers, 51.0 x 21.0 mm, 71 parts (11 on the bottom side), 61 nets.

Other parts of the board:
kibuzzard-66CE1AA2: G***; kibuzzard-66CE1AA2
kibuzzard-66CE1AF9: G***; kibuzzard-66CE1AF9
kibuzzard-631DCCC7: G***; kibuzzard-631DCCC7
kibuzzard-631DCD0C: G***; kibuzzard-631DCD0C
kibuzzard-631DCDA0: G***; kibuzzard-631DCDA0
kibuzzard-631DCDB3: G***; kibuzzard-631DCDB3
kibuzzard-631DCE60: G***; kibuzzard-631DCE60
kibuzzard-631DD065: G***; kibuzzard-631DD065
kibuzzard-631DD76C: G***; kibuzzard-631DD76C
kibuzzard-632CA15B: G***; kibuzzard-632CA15B
kibuzzard-660C3D9D: G***; kibuzzard-660C3D9D
kibuzzard-661291DB: G***; kibuzzard-661291DB
kibuzzard-661291DF: G***; kibuzzard-661291DF
kibuzzard-6612913A: G***; kibuzzard-6612913A
kibuzzard-66126165: G***; kibuzzard-66126165
kibuzzard-66129132: G***; kibuzzard-66129132

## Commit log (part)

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2024-08-29 V0.0.1 Initial Commit
    - Gerber files exported successfully.
    - Added `generateGerbers()` function.
    - Added Readme and Changes.
    - Added project info.
    - New Version `0.0.1`.
2024-08-29 V0.0.2
    - Added CLI argument parser.
    - Added `parseArguments()`.
    - Added `gerbers` command to export Gerber files.
    - `generateGerbers()` function now accepts the input PCB file name and the output directory path.
2024-08-29 V0.0.4
    - Output directory is now created if it does not exist, in `generateGerbers()` function.
    - KiCad-CLI commands will fail if the output directory does not exist.
2024-08-29 V0.0.6
    - Generated Gerber files are now renamed with the revision tag after the project name.
    - Gerber files are now compressed into a ZIP file using `zip_all_files()`.
2024-08-30 Added drill export
    - Added `generateDrills()`.
    - Drill files are now generated with the Gerbers.
    - All files in the Gerber target directory, except ZIP files are now deleted before overwriting. This fixes the rename conflicts.
    - If a ZIP file already exists, the new one will now get a new sequence number. This will keep single set of manufacturing files but multiple ZIP files.
    - New Version `0.0.7`.
2024-08-30 Added PCB PDF export
    - Added `generatePcbPdf()` to export the PCB as PDF files. Layers are imported in individual files with the `Edge.Cuts` as the common layer.
    - Added `pcb_pdf` command.
    - New Version `0.0.9`.
2024-09-01 Added schematic PDf export
    - Added `sch_pdf` export command. This will export the schematic as a single PDF.
    - Added `generateSchPdf()` function.
    - Schematic PDF generation is successful.
2024-09-01 Added BoM export
    - Added `bom` command to export BoM file. Only CSV is supported at the moment.
    - Added `generateBom()` function.
    - New Version `0.0.11`.
2024-09-01 Exported EXE v0.0.12
2024-09-01 Added ChatGPT credit
2024-09-02 Added support for JSON config
    - Added support for local JSON configuration file.
    - Updated `generateSchPdf()` to use output directory from the config file.
    - Added `load_config()` to load the custom and default configurations.
    - New Version `0.0.13`.
2024-09-02 Added full support for sch_pdf config
2024-09-03 Added `create_final_directory()` to create target directories
2024-09-04 Updated version string
2024-09-06 So many changes
    - Added `Colorize` and `_color` classes and `color` object to colorize text in the terminal.
    - Added text colors in multiple places for error messages, file names and commands.
    - `generateGerbers()` can now completely read the configuration from the `kiexport.json` file.
    - Added `delete_files()` function to delete files with the specified extensions, with inclusion and exclusion options.
    - Added `rename_files()` to rename files in a folder. It accepts the file extensions as a list.
    - Replaced `zip_all_files()` with `zip_all_files_2()`. The latter can now accept a list of file extensions to include in the zip file.
2024-09-06 generateGerbers() now generated drills
    - `generateGerbers()` now reads the configuration `kie_include_drill` and generated the drill files first based on the value. Default value is `true`.
    - New Version: `0.0.16`.
2024-10-06 Optimized the `generatePositions()` function
    - New Version `0.0.18`.
2024-10-06 Added JSON configuration support for `generateBom()`
    - New Version `0.0.20`.
2024-10-07 Fixed string quotes conflicts
    - New Version `0.0.21`.
2024-10-15 PCB PDF files are now saved as ZIP file also
    - New Version `0.0.23`.
2024-10-26 Udpated Readme
2024-11-02 Added PDF Merge Function for PCB PDF Files
2024-11-02 Udpated `merge_pdfs()`
    - Updated `merge_pdfs()`
    - Fixed indentation issues.
    - Fixed styling.
    - Updated debug message formats.
    - Disabled (commented out) deleting of original PDF files after merging.
    - Tested and working correctly.
2024-11-02 Updated JSON configuration
    - Updated `generateiBoM()`
    - `kicad_python_path` and `ibom_path` variables are now loaded from the `kiexport.json` file.
    - Bothe paths are now checked for existence.
    - Bumped up the `kiexport.json` JSON version to `1.1`.
    - Updated the default configuration.
2024-11-03 Simplified `load_config()`
    - Simplified `load_config()`.
    - Removed the extra `project_file` argument.
    - Now the configuration can be loaded as a relative or absolute path.
    - The default configuration file name will still be `kiexport.json`.
    - Added new `run` command and `run()` function.
    - This will generate files based on the provided JSON configuration file.
2024-11-03 Added documentation to `load_config()`
    - Added **# TODO:** Check the JSON configuration file version and warn about consequences.
2024-11-04 Exported EXE for version `0.0.26`
2024-11-05 Fixed fstring quotes mismatches
2024-11-08 Fixed app exiting on missing files
    - Removed unused libraries.
    - Fixed the issue of the app exiting when trying to generate files from PCB-only projects that do not have a schematic file in the project folder.
    - The app will now warn about the missing files (either schematic of PCB) and will skip the commands that require the missing files.
2024-11-08 Added SVG generation support
    - Added SVG generation support.
    - Added `generateSvg()` function.
    - Added `svg` command.
    - Updated the JSON with SVG generation options.
    - Tested and working.
    - New Version `0.0.27`.
2024-11-11 Fixed path issues in `generateiBoM()`
    - Fixed app exiting when either `kicad_python_path` or `ibom_path` are not found.
    - The `generateiBoM()` will now skip the command if either of the paths are not found.
    - Fixed whitespace handling in paths in `generateiBoM()` function.
2025-02-13 Enhanced the SVG generation
    - Added common layers support for SVG generation.
    - New `kie_common_layers` parameter under SVG configuration.
    - SVG files are now saved as ZIP file.
2025-02-20 Added new `kicad_cli_path` param
    - Added new `kicad_cli_path` configuration parameter.
    - This will help users to use different versions of KiCad CLI without adding it to the System Path.
    - `kicad_cli_path` will now be used by all generator functions.
    - JSON configuration version updated to `1.3`.
    - New Version 🆕 `v0.0.28`.
2025-04-11 The `run()` and `loadConfig()` functions check config path
    - The `run()` and `loadConfig()` functions now check if the provided parameter (filename or path) is a valid file.
    - If an invalid parameter is provided the user will be prompted to choose the default configuration.
2025-04-11 `run` command can now accept subset
    - `run` command can now accept a list of commands as the second parameter.
    - This will allow the user to provide a subset of commands to run from the configuration file.
2025-04-12 Added more docs
2025-04-12 New `pcb_render` command
    - Added support for new `pcb_render` command.
    - This can export the PCB as a rendered image with the help of KiCad V9's `pcb render` command.
    - Added support for `pcb_render` configuration in the `kiexport.json` file.
    - Added `generatePcbRenders()` function.
    - Incremented the `kiexport.json` version to `1.4`.
    - Updated Readme.
2025-04-12 Updated docs
2025-04-18 Adding KiCad V10 support
    - Changed reference project version to `v9.99`.
    - Created new branch 'V10-Support` to test KiCad V10 support.
    - Updated `kiexport.json`.
    - Added new render presets.
    - Changed KiCad CLI paths.
    - Updated `DEFAULT_CONFIG_JSON`.
2025-04-22 Fixed configuration lookup issue
    - Fixed configuration lookup issue.
    - Previously, the configuration lookup used to fail when the `DEFAULT_CONFIG_JSON` did not have the keys that are already in the user configuration.
    - The app used to lookup the configuration even when it was already found in the user configuration.
    - This has been fixed with the help of lazy loaded configuration.
    - Now, the default configuration is looked up only if something is not found in the user configuration.
    - Added `LazyDict` class to handle the lazy loading of the configuration.
2025-04-25 Improved logging
    - Improved logging.
    - The log file is now saved after all of the commands are executed.
    - Added `kiexport_log_path` to the configuration file.
    - The user can now pass the log file path and name through the configuration file.
    - Bumped up the KiExport configuration version to `1.5`.
2025-04-28 Fixed HTML BoM not populating custom fields
    - Fixed HTML BoM not populating the custom BoM fields.
    - This was due to the missing `--extra-data-file` field.
    - This field should have been provided with the source PCB file.
    - `generateiBoM()` now checks for this field and replaced the value with the source PCB file name.
    - Tested and working correctly.
    - New Version 🆕 `0.0.38`.
2025-05-07 Added XLS BoM support
    - Added support for generating XLS BoM.
    - Added `generateBomXls()`.
    - This function is dummy for now.
    - But the overall command processing logic has been implemented.
    - Unified all BoM generation commands under `bom`.
    - Removed the `ibom` command.
2025-05-08 Fixed empty argument errors
    - Fixed app printing errors due to mishandled logging when called without any arguments.
    - App will now simply exit when the arguments are empty.
2025-05-09 Updated command list in `validate_command_list()`
    - New Version 🆕 `0.1.2`.
2025-05-28 Added support for config version checking
    - Added support for version checking of the confguration JSON files.
    - Added `semver` library to handle version comparison.
    - Added `normalize_version()` to convert partial-semver versions to full-semver versions.
    - Added `MIN_CONFIG_JSON_VERSION` that tells the minimum version required.
    - When the current version is less than the minimum version, the `load_config()` will return `False` and subsequent operations will fail and exit.
    - When the current version is greater than or equal to the minimum version, the `load_config()` returns `True` but warns the user about the version mismatch.
2025-05-29 Fixed `generateBomXls()` function call issue
    - Fixed `generateBomXls()` function call issue in `parseArguments()`.
    - New Version 🆕 `0.1.5`.
2025-06-16 Updated `runDRC()`
    - Updated `runDRC()`.
    - It now checks how many voilations were found in the DRC report and print them.
    - If violations are found, the user will be prompted to continue or exit the app.
    - The export log won't be saved if the user chooses to exit. The report will still be saved.
    - `pcb_drc` command execcution will be set to false if the user chooses to continue with DRC errors.
    - New Version 🆕 `0.1.7`.
2025-06-16 Updated Readme
    - Updated Readme.
    - Added `pcb_drc` command documentation.
2025-06-16 Udpated
2025-10-05 Updated `merge_pdfs()`
    - `merge_pdfs()` can now accept a list of specific PDF files to merge.
    - If the list is not provided, all PDF files with `.pdf` extension in the folder will be merged.
    - This allows merging specific files when needed.
    - Fixed log message error in `generateBomXls()` function.
    - New Version 🆕 `0.1.9`.
2025-10-20 Added new options for the `gerbers` command
    - Added new options for the `gerbers` command.
    - Added `--sketch-pads-on-fab-layers`.
    - Added `--hide-DNP-footprints-on-fab-layers`.
    - Added `--sketch-DNP-footprints-on-fab-layers`.
    - Added `--crossout-DNP-footprints-on-fab-layers`.
    - Added `--plot-invisible-text`.
2025-10-24 Added support for exporting rendered SVG images
    - Added support for exporting rendered SVG images.
    - Updated the `kiexport.json` specification.
    - Updated the JSON version to `1.8`.
    - Added `vtracer_path`.
    - This tells where the VTracer SVG converter is located.
    - This can be a full path or jus the executable name if it is in the System Path.
2025-10-24 Updated `generatePcbReners()`
    - Reverted the `MIN_CONFIG_JSON_VERSION` value back to `1.7`.
    - I tested the current version with `1.7` and found no issues.
    - Updated `generatePcbReners()`.
    - `kie_generate_svg` is no longer loaded with a default value.
    - Such control flags must only be read from the configuration file.
    - Added exception handling for missing `kie_generate_svg` key.

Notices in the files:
Readme.md:
License:
This project is licensed under the MIT license.
Mitayi-Pico-D1/Mitayi-Pico-D1.kicad_pcb:
Released under MIT Open-source License
parts and their libraries:
License: CC BY 4.0
